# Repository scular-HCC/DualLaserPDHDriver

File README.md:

# Dual-Laser PDH Driver

**A precision two-channel controller for 1550 nm DFB butterfly lasers — a differential optical thermometer built as a 3U Eurocard instrument.**

Each channel provides low-noise constant-current laser drive, a bipolar linear TEC temperature controller, RF frequency modulation, and a synchronous-demodulation Pound–Drever–Hall lock that holds the laser to the side of an optical resonance. Lasers A and B lock to their own fringe of a shared reference cavity; the beat frequency between them, Δν = S·(T_B − T_A) with S ≈ 2 GHz/K, is a ratiometric measurement in which slow common-mode drift cancels.

## Highlights

| | |
|---|---|
| **2×** | 1550 nm DFB laser channels |
| **≈2 GHz/K** | beat sensitivity |
| **4–40 nK** | 60 s stability (equivalent-kelvin Allan deviation) |
| **±2.5 A** | bipolar linear TEC per channel |
| **8-slot** | 3U passive backplane, card-based architecture |

The RF analog-derivative lock this hardware runs targets the ≈4–11 nK regime, limited primarily by the laser's residual amplitude modulation (RAM), not by the electronics.

## ⚠️ Safety

This is a mains-powered Class 3B/4 laser instrument. Before working on it, read [Section 02 of the User Manual](docs/laser_driver_v5_user_manual.html). In brief:

- **Mains voltage** — the AC board and toroidal transformers carry 120 VAC. Only qualified personnel should open the enclosure with power applied; do not defeat the IEC inlet fuse or SL22 inrush thermistor.
- **Invisible 1550 nm laser radiation** — can damage the retina. Never look into a fiber connector or butterfly output; cap unused fibers; follow your site's laser-safety procedures.
- **Laser reverse voltage** — the DFB die tolerates only ≈2 V reverse. The per-channel BAT46W Schottky clamp is mandatory; confirm polarity before first power-on.
- **Live heatsinks** — on the pm22V and pm6V supplies the pass-transistor tabs sit at the raw rail (up to ≈±28 V), not ground. Isolate or keep them clear.

## Architecture

The instrument is a set of interchangeable cards on a passive 3U backplane, each in a universal slot with on-card jumper addressing:

- **AC Board** — mains entry, IEC inlet, transformers
- **pm22V / pm6V / pm1p8V** — linear power supplies (±18 V, ±6 V TEC, low-voltage rails)
- **DIG card** — Teensy-based controller, web dashboard, fault handling
- **CH card ×2** — per-channel laser constant-current drive + bipolar TEC
- **AFE card** — analog detection / synchronous-demodulation front end

## Documentation

| Document | Contents |
|---|---|
| **[User Manual (v5)](docs/laser_driver_v5_user_manual.html)** | Full theory of operation, per-card reference, software, bring-up, uncertainty budget |
| [Firmware reference](docs/firmware_reference.html) | Teensy firmware, command set, lock state machine |
| [Power review](docs/laser_driver_v5_power_review.html) | Supply analysis |
| [Project summary](Dual-Laser_PDH_Driver_Summary.pdf) | One-document overview (PDF) |

> The HTML docs are styled pages — they render best via GitHub Pages or by opening the file locally. On GitHub the raw source is shown when clicked.

## Repository layout

This repository spans several design generations. **`Lasser_Driver_v5/` is the current, card-based design** that the User Manual describes. `Laser_Driver_v3/` and `Laser_Driver_v4/` are earlier monolithic/mains prototypes retained for reference. Firmware lives in `Teensy/`, and all documentation is in `docs/`.

## License

Copyright © 2026 Stefan Cular. All rights reserved. See [LICENSE](LICENSE).
This project is published for reference and viewing only; no reuse is permitted without written permission.

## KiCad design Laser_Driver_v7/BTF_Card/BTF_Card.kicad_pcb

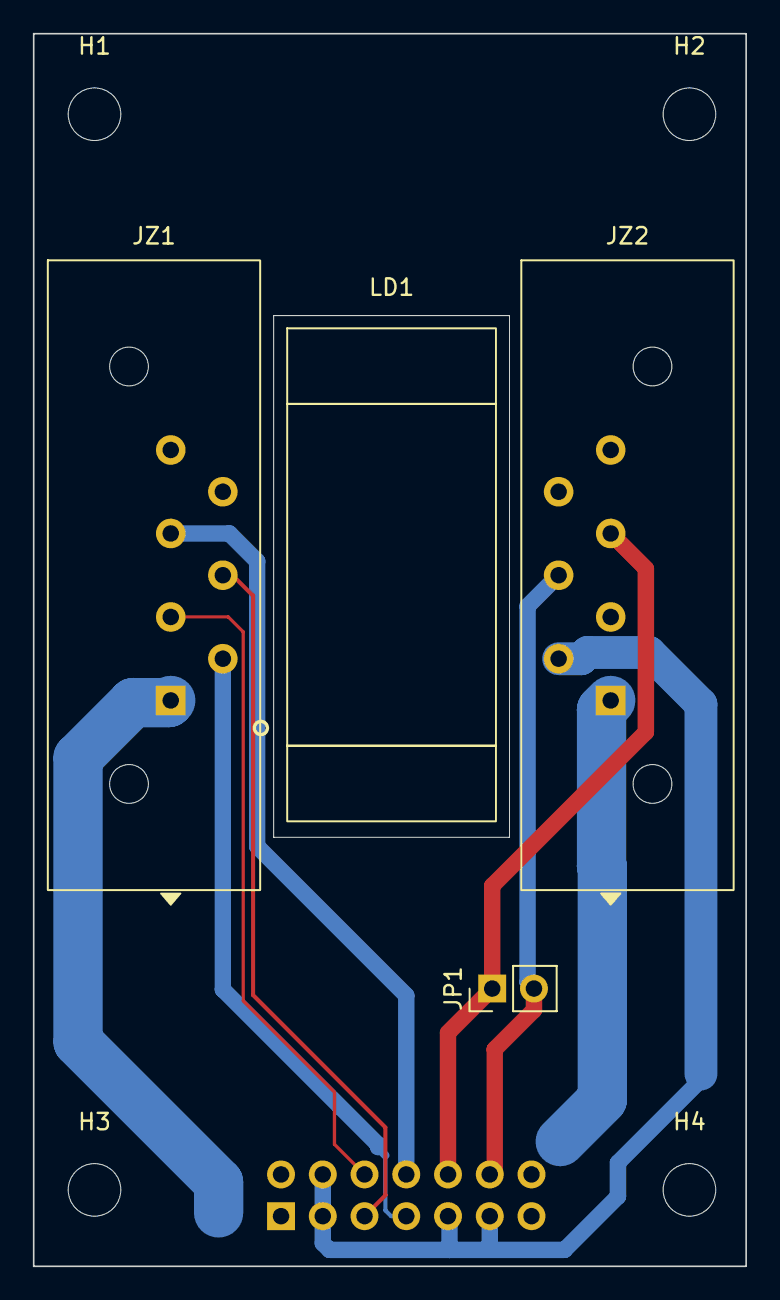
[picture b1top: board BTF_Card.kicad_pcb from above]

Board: 2 copper layers, 43.4 x 75.0 mm, 9 parts (1 on the bottom side), 9 nets.

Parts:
H1, H2, H3, H4: M3; MountingHole_3.2mm_M3
J1: ESQ-107-12-G-D; PinSocket_2x07_P2.54mm_Vertical
JP1: LD SHORT; PinHeader_1x02_P2.54mm_Vertical
JZ1: Azimuth 5253-100-7S; Azimuth_5253-100-7S_ButterflyZIF
JZ2: Azimuth 5253-100-7R; Azimuth_5253-100-7R_ButterflyZIF
LD1: DFB1550LP; DFB1550LP_Butterfly14_Mech

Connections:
CASE: J1.3, J1.4, J1.9, J1.11, JZ2.2
LD_A: J1.10, JP1.1 (A), JZ2.5
LD_K: J1.12, JP1.2 (B), JZ2.4
MPD_A: J1.6, JZ1.3
MPD_K: J1.5, JZ1.4
NTC_A: J1.7, JZ1.2
NTC_GND: J1.8, JZ1.5
TEC_N: J1.13, J1.14, JZ2.1
TEC_P: J1.1, J1.2, JZ1.1

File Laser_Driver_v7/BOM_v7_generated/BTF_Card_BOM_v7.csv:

Quantity,Manufacturer Part Number,Manufacturer,Customer Reference,Value,Footprint
1,ESQ-107-12-G-D,Samtec,J1,ESQ-107-12-G-D,PinSocket_2x07_P2.54mm_Vertical
1,61300211121,Wurth Elektronik,JP1,LD SHORT,PinHeader_1x02_P2.54mm_Vertical
1,5253-100-7S,Azimuth Electronics,JZ1,Azimuth 5253-100-7S,Azimuth_5253-100-7S_ButterflyZIF
1,5253-100-7R,Azimuth Electronics,JZ2,Azimuth 5253-100-7R,Azimuth_5253-100-7R_ButterflyZIF

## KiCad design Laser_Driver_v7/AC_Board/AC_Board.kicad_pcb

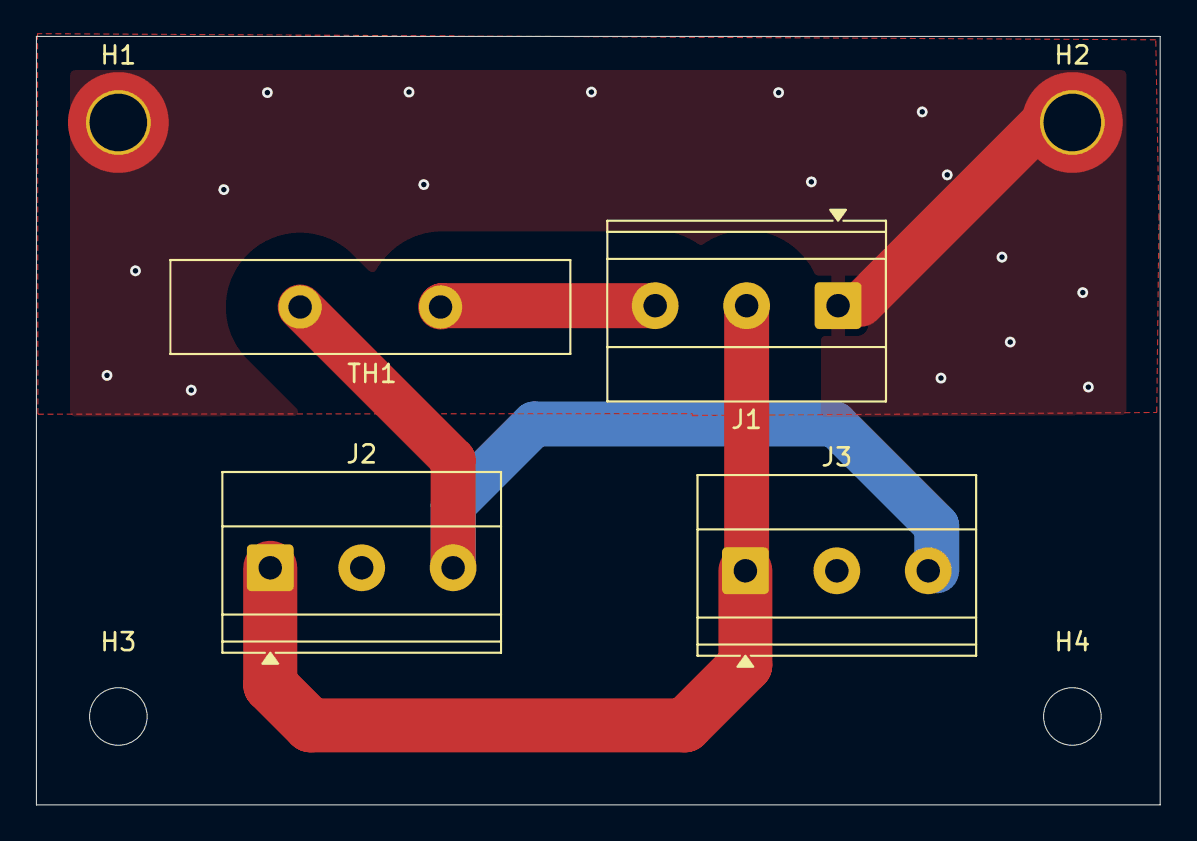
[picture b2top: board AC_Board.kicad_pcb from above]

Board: 2 copper layers, 62.4 x 42.7 mm, 8 parts (0 on the bottom side), 4 nets.

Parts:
H1, H2: MountingHole_Pad; MountingHole_3.2mm_M3_DIN965_Pad_TopBottom
H3, H4: MountingHole; MountingHole_3.2mm_M3
J1, J2, J3: Screw_Terminal_01x03; TerminalBlock_Phoenix_MKDS-1,5-3-5.08_1x03_P5.08mm_Horizont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
TH1: Ametherm SL22 10005; Thermistor_Disc_D22.0mm_W5.0mm_P7.80mm_Ametherm_SL22

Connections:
120Vac: J1.3, TH1.1
/Line_TH: J2.3, J3.3, TH1.2
Earth: H1.1 (1_1), H2.1 (1_1), J1.1
Neutral: J1.2, J2.1, J3.1

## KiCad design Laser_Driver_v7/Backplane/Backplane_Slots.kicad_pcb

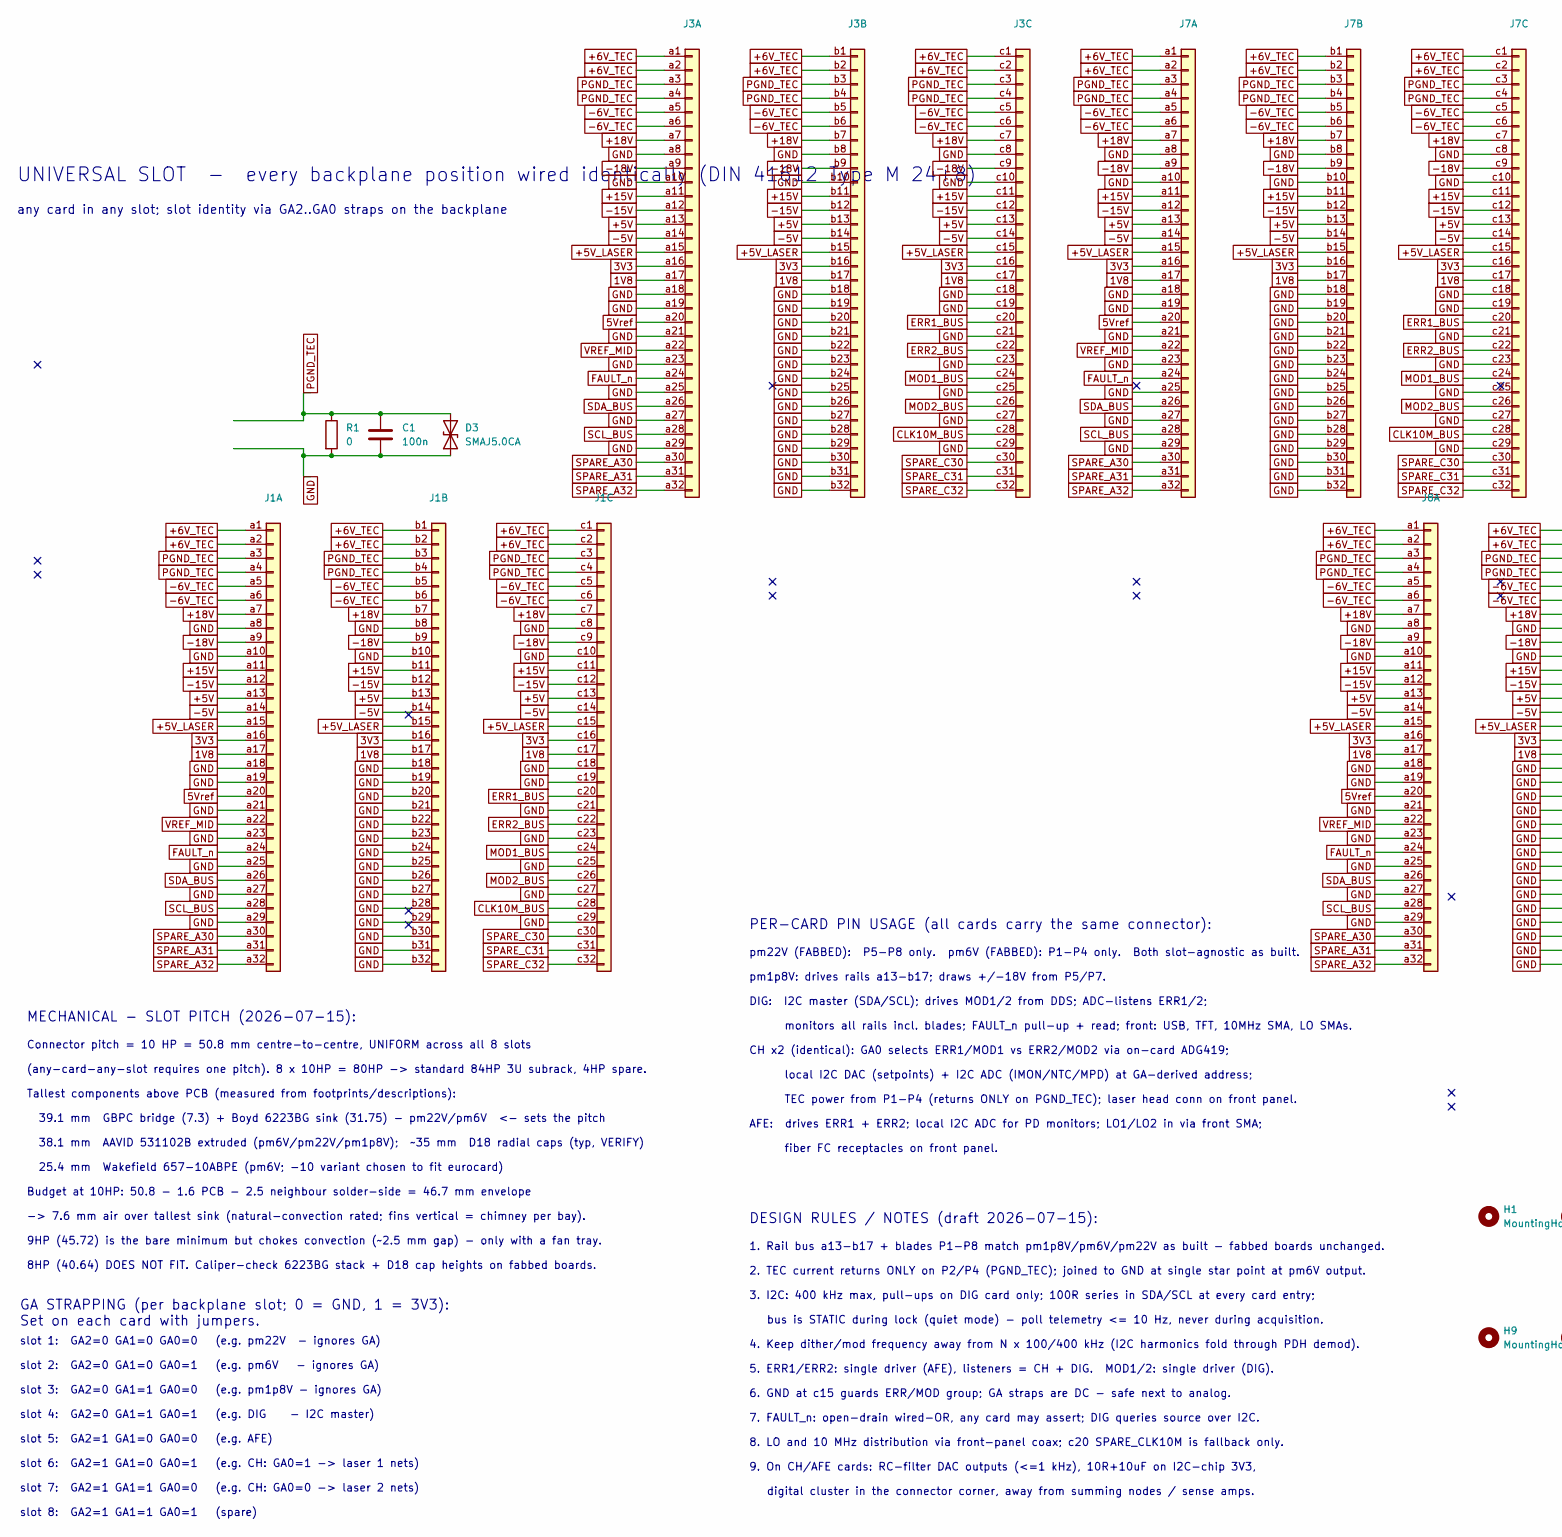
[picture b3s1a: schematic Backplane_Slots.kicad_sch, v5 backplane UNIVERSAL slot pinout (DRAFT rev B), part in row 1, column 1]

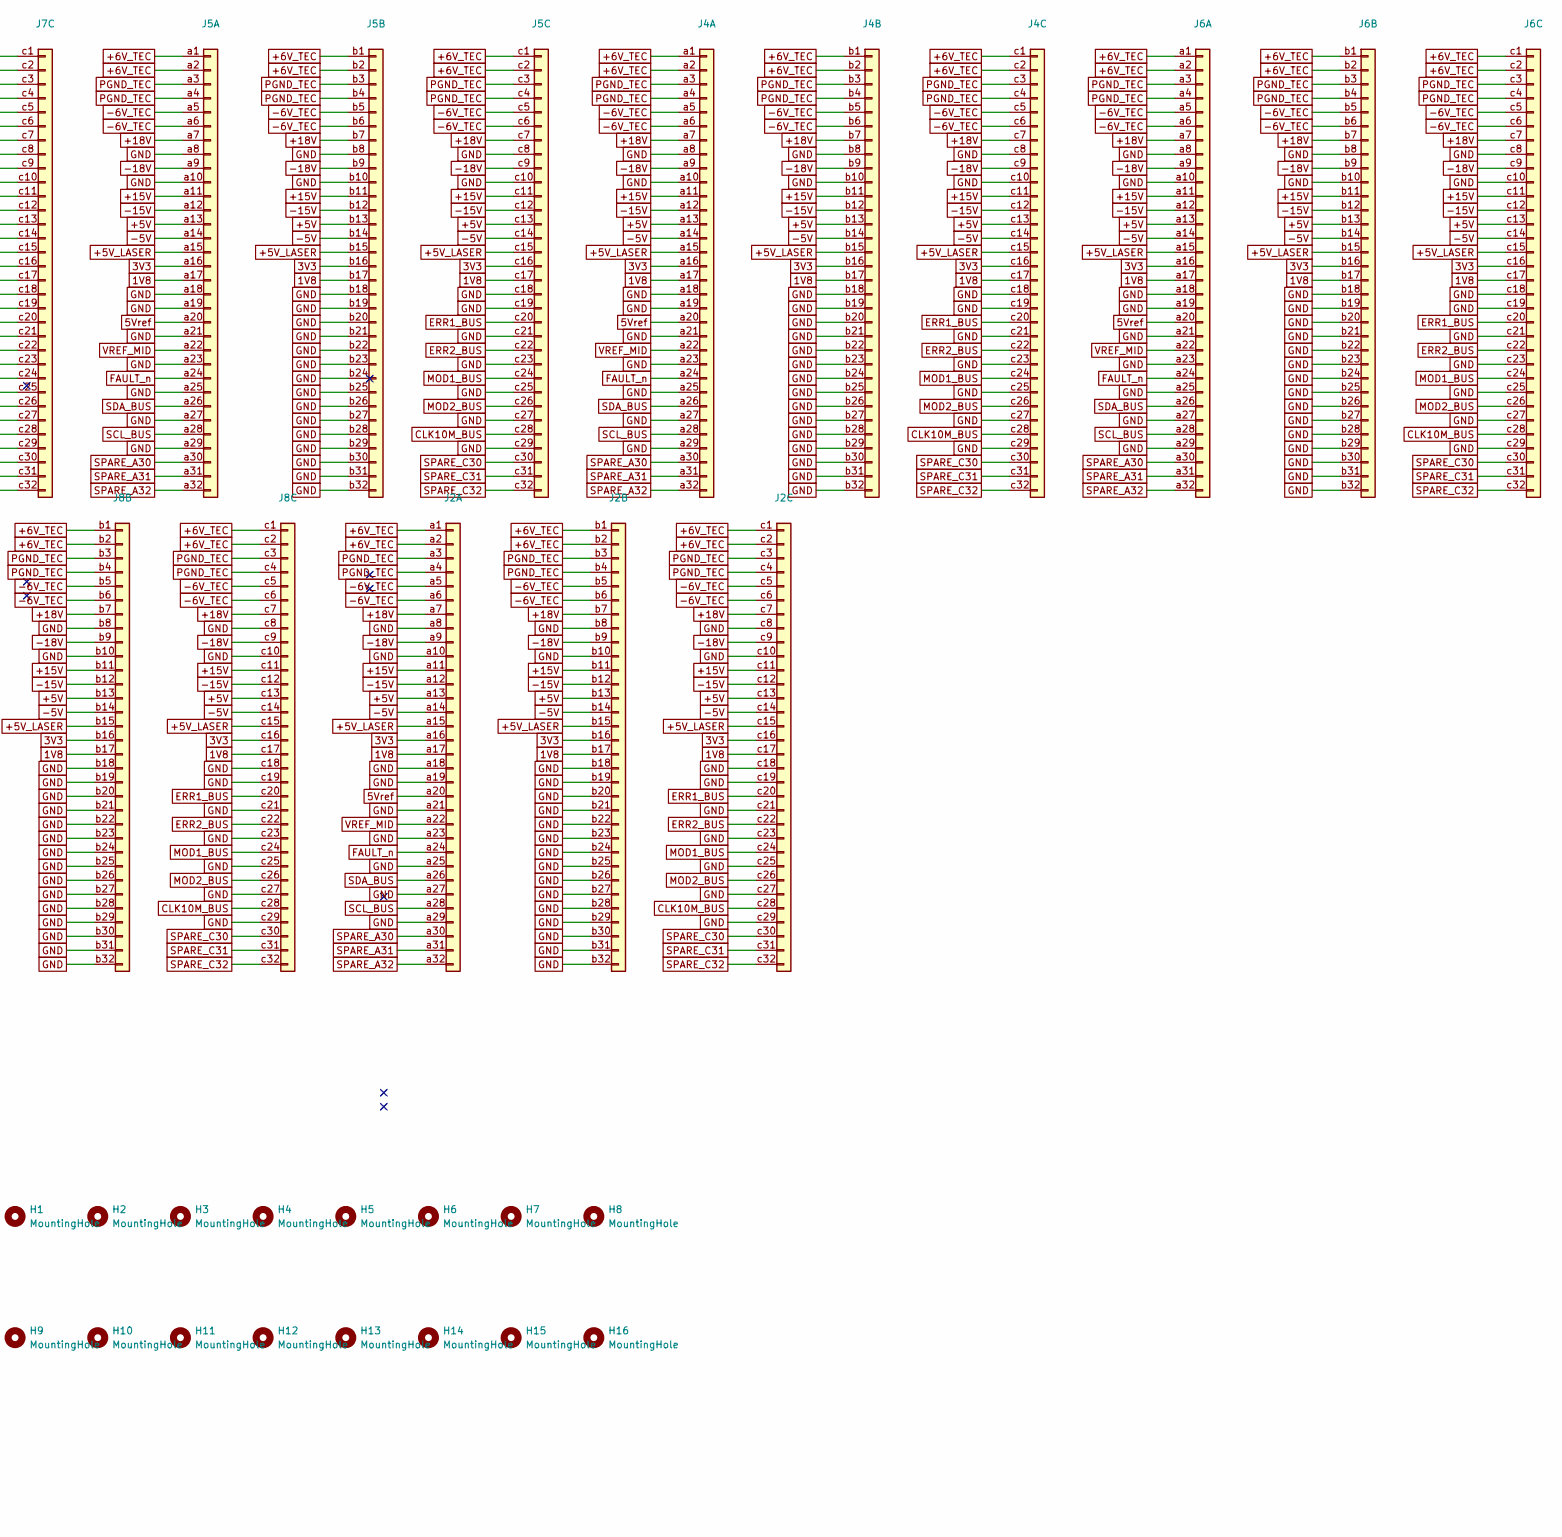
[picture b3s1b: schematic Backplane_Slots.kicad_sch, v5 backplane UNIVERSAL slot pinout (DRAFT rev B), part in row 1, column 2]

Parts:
C1: 100n; C_0805_2012Metric_Pad1.18x1.45mm_HandSolder
D3: SMAJ5.0CA; D_SMA-SMB_Universal_Handsoldering; MPN SMAJ5.0CA-E3/61
H1, H2, H3, H4, H5, H6, H7, H8, H9, H10, H11, H12, H13, H14, H15, H16: MountingHole; MountingHole_2.7mm
J1, J2, J3, J4, J5, J6, J7, J8: DIN41612_03x32_C_Split; DIN41612_C_3x32_Female_Vertical_THT
R1: 0; R_0805_2012Metric_Pad1.20x1.40mm_HandSolder

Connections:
1V8: J1.a17, J1.b17, J1.c17, J2.a17, J2.b17, J2.c17, J3.a17, J3.b17, J3.c17, J4.a17, J4.b17, J4.c17, J5.a17, J5.b17, J5.c17, J6.a17, J6.b17, J6.c17, J7.a17, J7.b17, J7.c17, J8.a17, J8.b17, J8.c17
3V3: J1.a16, J1.b16, J1.c16, J2.a16, J2.b16, J2.c16, J3.a16, J3.b16, J3.c16, J4.a16, J4.b16, J4.c16, J5.a16, J5.b16, J5.c16, J6.a16, J6.b16, J6.c16, J7.a16, J7.b16, J7.c16, J8.a16, J8.b16, J8.c16
5Vref: J1.a20, J2.a20, J3.a20, J4.a20, J5.a20, J6.a20, J7.a20, J8.a20
+5V: J1.a13, J1.b13, J1.c13, J2.a13, J2.b13, J2.c13, J3.a13, J3.b13, J3.c13, J4.a13, J4.b13, J4.c13, J5.a13, J5.b13, J5.c13, J6.a13, J6.b13, J6.c13, J7.a13, J7.b13, J7.c13, J8.a13, J8.b13, J8.c13
+5V_LASER: J1.a15, J1.b15, J1.c15, J2.a15, J2.b15, J2.c15, J3.a15, J3.b15, J3.c15, J4.a15, J4.b15, J4.c15, J5.a15, J5.b15, J5.c15, J6.a15, J6.b15, J6.c15, J7.a15, J7.b15, J7.c15, J8.a15, J8.b15, J8.c15
+6V_TEC: J1.a1, J1.a2, J1.b1, J1.b2, J1.c1, J1.c2, J2.a1, J2.a2, J2.b1, J2.b2, J2.c1, J2.c2, J3.a1, J3.a2, J3.b1, J3.b2, J3.c1, J3.c2, J4.a1, J4.a2, J4.b1, J4.b2, J4.c1, J4.c2, J5.a1, J5.a2, J5.b1, J5.b2, J5.c1, J5.c2, J6.a1, J6.a2, J6.b1, J6.b2, J6.c1, J6.c2, J7.a1, J7.a2, J7.b1, J7.b2, J7.c1, J7.c2, J8.a1, J8.a2, J8.b1, J8.b2, J8.c1, J8.c2
+15V: J1.a11, J1.b11, J1.c11, J2.a11, J2.b11, J2.c11, J3.a11, J3.b11, J3.c11, J4.a11, J4.b11, J4.c11, J5.a11, J5.b11, J5.c11, J6.a11, J6.b11, J6.c11, J7.a11, J7.b11, J7.c11, J8.a11, J8.b11, J8.c11
+18V: J1.a7, J1.b7, J1.c7, J2.a7, J2.b7, J2.c7, J3.a7, J3.b7, J3.c7, J4.a7, J4.b7, J4.c7, J5.a7, J5.b7, J5.c7, J6.a7, J6.b7, J6.c7, J7.a7, J7.b7, J7.c7, J8.a7, J8.b7, J8.c7
-5V: J1.a14, J1.b14, J1.c14, J2.a14, J2.b14, J2.c14, J3.a14, J3.b14, J3.c14, J4.a14, J4.b14, J4.c14, J5.a14, J5.b14, J5.c14, J6.a14, J6.b14, J6.c14, J7.a14, J7.b14, J7.c14, J8.a14, J8.b14, J8.c14
-6V_TEC: J1.a5, J1.a6, J1.b5, J1.b6, J1.c5, J1.c6, J2.a5, J2.a6, J2.b5, J2.b6, J2.c5, J2.c6, J3.a5, J3.a6, J3.b5, J3.b6, J3.c5, J3.c6, J4.a5, J4.a6, J4.b5, J4.b6, J4.c5, J4.c6, J5.a5, J5.a6, J5.b5, J5.b6, J5.c5, J5.c6, J6.a5, J6.a6, J6.b5, J6.b6, J6.c5, J6.c6, J7.a5, J7.a6, J7.b5, J7.b6, J7.c5, J7.c6, J8.a5, J8.a6, J8.b5, J8.b6, J8.c5, J8.c6
-15V: J1.a12, J1.b12, J1.c12, J2.a12, J2.b12, J2.c12, J3.a12, J3.b12, J3.c12, J4.a12, J4.b12, J4.c12, J5.a12, J5.b12, J5.c12, J6.a12, J6.b12, J6.c12, J7.a12, J7.b12, J7.c12, J8.a12, J8.b12, J8.c12
-18V: J1.a9, J1.b9, J1.c9, J2.a9, J2.b9, J2.c9, J3.a9, J3.b9, J3.c9, J4.a9, J4.b9, J4.c9, J5.a9, J5.b9, J5.c9, J6.a9, J6.b9, J6.c9, J7.a9, J7.b9, J7.c9, J8.a9, J8.b9, J8.c9
CLK10M_BUS: J1.c28, J2.c28, J3.c28, J4.c28, J5.c28, J6.c28, J7.c28, J8.c28
ERR1_BUS: J1.c20, J2.c20, J3.c20, J4.c20, J5.c20, J6.c20, J7.c20, J8.c20
ERR2_BUS: J1.c22, J2.c22, J3.c22, J4.c22, J5.c22, J6.c22, J7.c22, J8.c22
FAULT_n: J1.a24, J2.a24, J3.a24, J4.a24, J5.a24, J6.a24, J7.a24, J8.a24
GND: C1.2, D3.1 (A1), J1.a8, J1.a10, J1.a18, J1.a19, J1.a21, J1.a23, J1.a25, J1.a27, J1.a29, J1.b8, J1.b10, J1.b18, J1.b19, J1.b20, J1.b21, J1.b22, J1.b23, J1.b24, J1.b25, J1.b26, J1.b27, J1.b28, J1.b29, J1.b30, J1.b31, J1.b32, J1.c8, J1.c10, J1.c18, J1.c19, J1.c21, J1.c23, J1.c25, J1.c27, J1.c29, J2.a8, J2.a10, J2.a18, J2.a19, J2.a21, J2.a23, J2.a25, J2.a27, J2.a29, J2.b8, J2.b10, J2.b18, J2.b19, J2.b20, J2.b21, J2.b22, J2.b23, J2.b24, J2.b25, J2.b26, J2.b27, J2.b28, J2.b29, J2.b30, J2.b31, J2.b32, J2.c8, J2.c10, J2.c18, J2.c19, J2.c21, J2.c23, J2.c25, J2.c27, J2.c29, J3.a8, J3.a10, J3.a18, J3.a19, J3.a21, J3.a23, J3.a25, J3.a27, J3.a29, J3.b8, J3.b10, J3.b18, J3.b19, J3.b20, J3.b21, J3.b22, J3.b23, J3.b24, J3.b25, J3.b26, J3.b27, J3.b28, J3.b29, J3.b30, J3.b31, J3.b32, J3.c8, J3.c10, J3.c18, J3.c19, J3.c21, J3.c23, J3.c25, J3.c27, J3.c29, J4.a8, J4.a10, J4.a18, J4.a19, J4.a21, J4.a23, J4.a25, J4.a27, J4.a29, J4.b8, J4.b10, J4.b18, J4.b19, J4.b20, J4.b21, J4.b22, J4.b23, J4.b24, J4.b25, J4.b26, J4.b27, J4.b28, J4.b29, J4.b30, J4.b31, J4.b32, J4.c8, J4.c10, J4.c18, J4.c19, J4.c21, J4.c23, J4.c25, J4.c27, J4.c29, J5.a8, J5.a10, J5.a18, J5.a19, J5.a21, J5.a23, J5.a25, J5.a27, J5.a29, J5.b8, J5.b10, J5.b18, J5.b19, J5.b20, J5.b21, J5.b22, J5.b23, J5.b24, J5.b25, J5.b26, J5.b27, J5.b28, J5.b29, J5.b30, J5.b31, J5.b32, J5.c8, J5.c10, J5.c18, J5.c19, J5.c21, J5.c23, J5.c25, J5.c27, J5.c29, J6.a8, J6.a10, J6.a18, J6.a19, J6.a21, J6.a23, J6.a25, J6.a27, J6.a29, J6.b8, J6.b10, J6.b18, J6.b19, J6.b20, J6.b21, J6.b22, J6.b23, J6.b24, J6.b25, J6.b26, J6.b27, J6.b28, J6.b29, J6.b30, J6.b31, J6.b32, J6.c8, J6.c10, J6.c18, J6.c19, J6.c21, J6.c23, J6.c25, J6.c27, J6.c29, J7.a8, J7.a10, J7.a18, J7.a19, J7.a21, J7.a23, J7.a25, J7.a27, J7.a29, J7.b8, J7.b10, J7.b18, J7.b19, J7.b20, J7.b21, J7.b22, J7.b23, J7.b24, J7.b25, J7.b26, J7.b27, J7.b28, J7.b29, J7.b30, J7.b31, J7.b32, J7.c8, J7.c10, J7.c18, J7.c19, J7.c21, J7.c23, J7.c25, J7.c27, J7.c29, J8.a8, J8.a10, J8.a18, J8.a19, J8.a21, J8.a23, J8.a25, J8.a27, J8.a29, J8.b8, J8.b10, J8.b18, J8.b19, J8.b20, J8.b21, J8.b22, J8.b23, J8.b24, J8.b25, J8.b26, J8.b27, J8.b28, J8.b29, J8.b30, J8.b31, J8.b32, J8.c8, J8.c10, J8.c18, J8.c19, J8.c21, J8.c23, J8.c25, J8.c27, J8.c29, R1.2
MOD1_BUS: J1.c24, J2.c24, J3.c24, J4.c24, J5.c24, J6.c24, J7.c24, J8.c24
MOD2_BUS: J1.c26, J2.c26, J3.c26, J4.c26, J5.c26, J6.c26, J7.c26, J8.c26
PGND_TEC: C1.1, D3.2 (A2), J1.a3, J1.a4, J1.b3, J1.b4, J1.c3, J1.c4, J2.a3, J2.a4, J2.b3, J2.b4, J2.c3, J2.c4, J3.a3, J3.a4, J3.b3, J3.b4, J3.c3, J3.c4, J4.a3, J4.a4, J4.b3, J4.b4, J4.c3, J4.c4, J5.a3, J5.a4, J5.b3, J5.b4, J5.c3, J5.c4, J6.a3, J6.a4, J6.b3, J6.b4, J6.c3, J6.c4, J7.a3, J7.a4, J7.b3, J7.b4, J7.c3, J7.c4, J8.a3, J8.a4, J8.b3, J8.b4, J8.c3, J8.c4, R1.1
SCL_BUS: J1.a28, J2.a28, J3.a28, J4.a28, J5.a28, J6.a28, J7.a28, J8.a28
SDA_BUS: J1.a26, J2.a26, J3.a26, J4.a26, J5.a26, J6.a26, J7.a26, J8.a26
SPARE_A30: J1.a30, J2.a30, J3.a30, J4.a30, J5.a30, J6.a30, J7.a30, J8.a30
SPARE_A31: J1.a31, J2.a31, J3.a31, J4.a31, J5.a31, J6.a31, J7.a31, J8.a31
SPARE_A32: J1.a32, J2.a32, J3.a32, J4.a32, J5.a32, J6.a32, J7.a32, J8.a32
SPARE_C30: J1.c30, J2.c30, J3.c30, J4.c30, J5.c30, J6.c30, J7.c30, J8.c30
SPARE_C31: J1.c31, J2.c31, J3.c31, J4.c31, J5.c31, J6.c31, J7.c31, J8.c31
SPARE_C32: J1.c32, J2.c32, J3.c32, J4.c32, J5.c32, J6.c32, J7.c32, J8.c32
VREF_MID: J1.a22, J2.a22, J3.a22, J4.a22, J5.a22, J6.a22, J7.a22, J8.a22

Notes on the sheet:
pm22V (FABBED): P5-P8 only. pm6V (FABBED): P1-P4 only. Both slot-agnostic as built.
DIG: I2C master (SDA/SCL); drives MOD1/2 from DDS; ADC-listens ERR1/2;
2. TEC current returns ONLY on P2/P4 (PGND_TEC); joined to GND at single star point at pm6V output.
8. LO and 10 MHz distribution via front-panel coax; c20 SPARE_CLK10M is fallback only.
AFE: drives ERR1 + ERR2; local I2C ADC for PD monitors; LO1/LO2 in via front SMA;
6. GND at c15 guards ERR/MOD group; GA straps are DC - safe next to analog.
38.1 mm AAVID 531102B extruded (pm6V/pm22V/pm1p8V); ~35 mm D18 radial caps (typ, VERIFY)
TEC power from P1-P4 (returns ONLY on PGND_TEC); laser head conn on front panel.
slot 5: GA2=1 GA1=0 GA0=0 (e.g. AFE)
slot 3: GA2=0 GA1=1 GA0=0 (e.g. pm1p8V - ignores GA)
PER-CARD PIN USAGE (all cards carry the same connector):
any card in any slot; slot identity via GA2..GA0 straps on the backplane
Budget at 10HP: 50.8 - 1.6 PCB - 2.5 neighbour solder-side = 46.7 mm envelope
(any-card-any-slot requires one pitch). 8 x 10HP = 80HP -> standard 84HP 3U subrack, 4HP spare.
1. Rail bus a13-b17 + blades P1-P8 match pm1p8V/pm6V/pm22V as built - fabbed boards unchanged.
slot 6: GA2=1 GA1=0 GA0=1 (e.g. CH: GA0=1 -> laser 1 nets)
slot 7: GA2=1 GA1=1 GA0=0 (e.g. CH: GA0=0 -> laser 2 nets)
bus is STATIC during lock (quiet mode) - poll telemetry <= 10 Hz, never during acquisition.
8HP (40.64) DOES NOT FIT. Caliper-check 6223BG stack + D18 cap heights on fabbed boards.
slot 4: GA2=0 GA1=1 GA0=1 (e.g. DIG - I2C master)
4. Keep dither/mod frequency away from N x 100/400 kHz (I2C harmonics fold through PDH demod).
slot 8: GA2=1 GA1=1 GA0=1 (spare)
Tallest components above PCB (measured from footprints/descriptions):
MECHANICAL - SLOT PITCH (2026-07-15):
GA STRAPPING (per backplane slot; 0 = GND, 1 = 3V3): Set on each card with jumpers.
local I2C DAC (setpoints) + I2C ADC (IMON/NTC/MPD) at GA-derived address;
39.1 mm GBPC bridge (7.3) + Boyd 6223BG sink (31.75) - pm22V/pm6V <- sets the pitch
DESIGN RULES / NOTES (draft 2026-07-15):
25.4 mm Wakefield 657-10ABPE (pm6V; -10 variant chosen to fit eurocard)
9. On CH/AFE cards: RC-filter DAC outputs (<=1 kHz), 10R+10uF on I2C-chip 3V3,
digital cluster in the connector corner, away from summing nodes / sense amps.
-> 7.6 mm air over tallest sink (natural-convection rated; fins vertical = chimney per bay).
7. FAULT_n: open-drain wired-OR, any card may assert; DIG queries source over I2C.
Connector pitch = 10 HP = 50.8 mm centre-to-centre, UNIFORM across all 8 slots
slot 2: GA2=0 GA1=0 GA0=1 (e.g. pm6V - ignores GA)
monitors all rails incl. blades; FAULT_n pull-up + read; front: USB, TFT, 10MHz SMA, LO SMAs.
CH x2 (identical): GA0 selects ERR1/MOD1 vs ERR2/MOD2 via on-card ADG419;
slot 1: GA2=0 GA1=0 GA0=0 (e.g. pm22V - ignores GA)
UNIVERSAL SLOT - every backplane position wired identically (DIN 41612 Type M 24+8)
fiber FC receptacles on front panel.

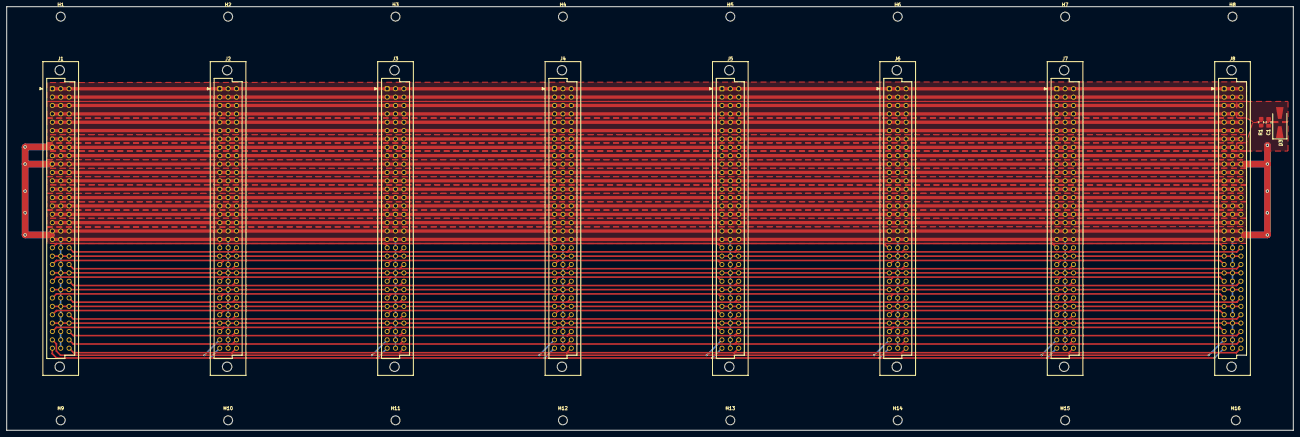
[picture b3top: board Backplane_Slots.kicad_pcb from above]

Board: 2 copper layers, 390.4 x 128.6 mm, 27 parts (0 on the bottom side), 29 nets.

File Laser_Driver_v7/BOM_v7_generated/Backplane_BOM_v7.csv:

Quantity,Manufacturer Part Number,Manufacturer,Customer Reference,Value,Footprint
1,CL21B104KBCNNNC,Samsung Electro-Mechanics,C1,100n,C_0805_2012Metric_Pad1.18x1.45mm_HandSolder
1,SMAJ5.0CA-E3/61,,D3,SMAJ5.0CA,D_SMA-SMB_Universal_Handsoldering
8,09032966855,HARTING,"J1,J2,J3,J4,J5,J6,J7,J8",DIN41612_03x32_C_Split,DIN41612_C_3x32_Female_Vertical_THT
1,RC0805JR-070RL,YAGEO,R1,0,R_0805_2012Metric_Pad1.20x1.40mm_HandSolder
